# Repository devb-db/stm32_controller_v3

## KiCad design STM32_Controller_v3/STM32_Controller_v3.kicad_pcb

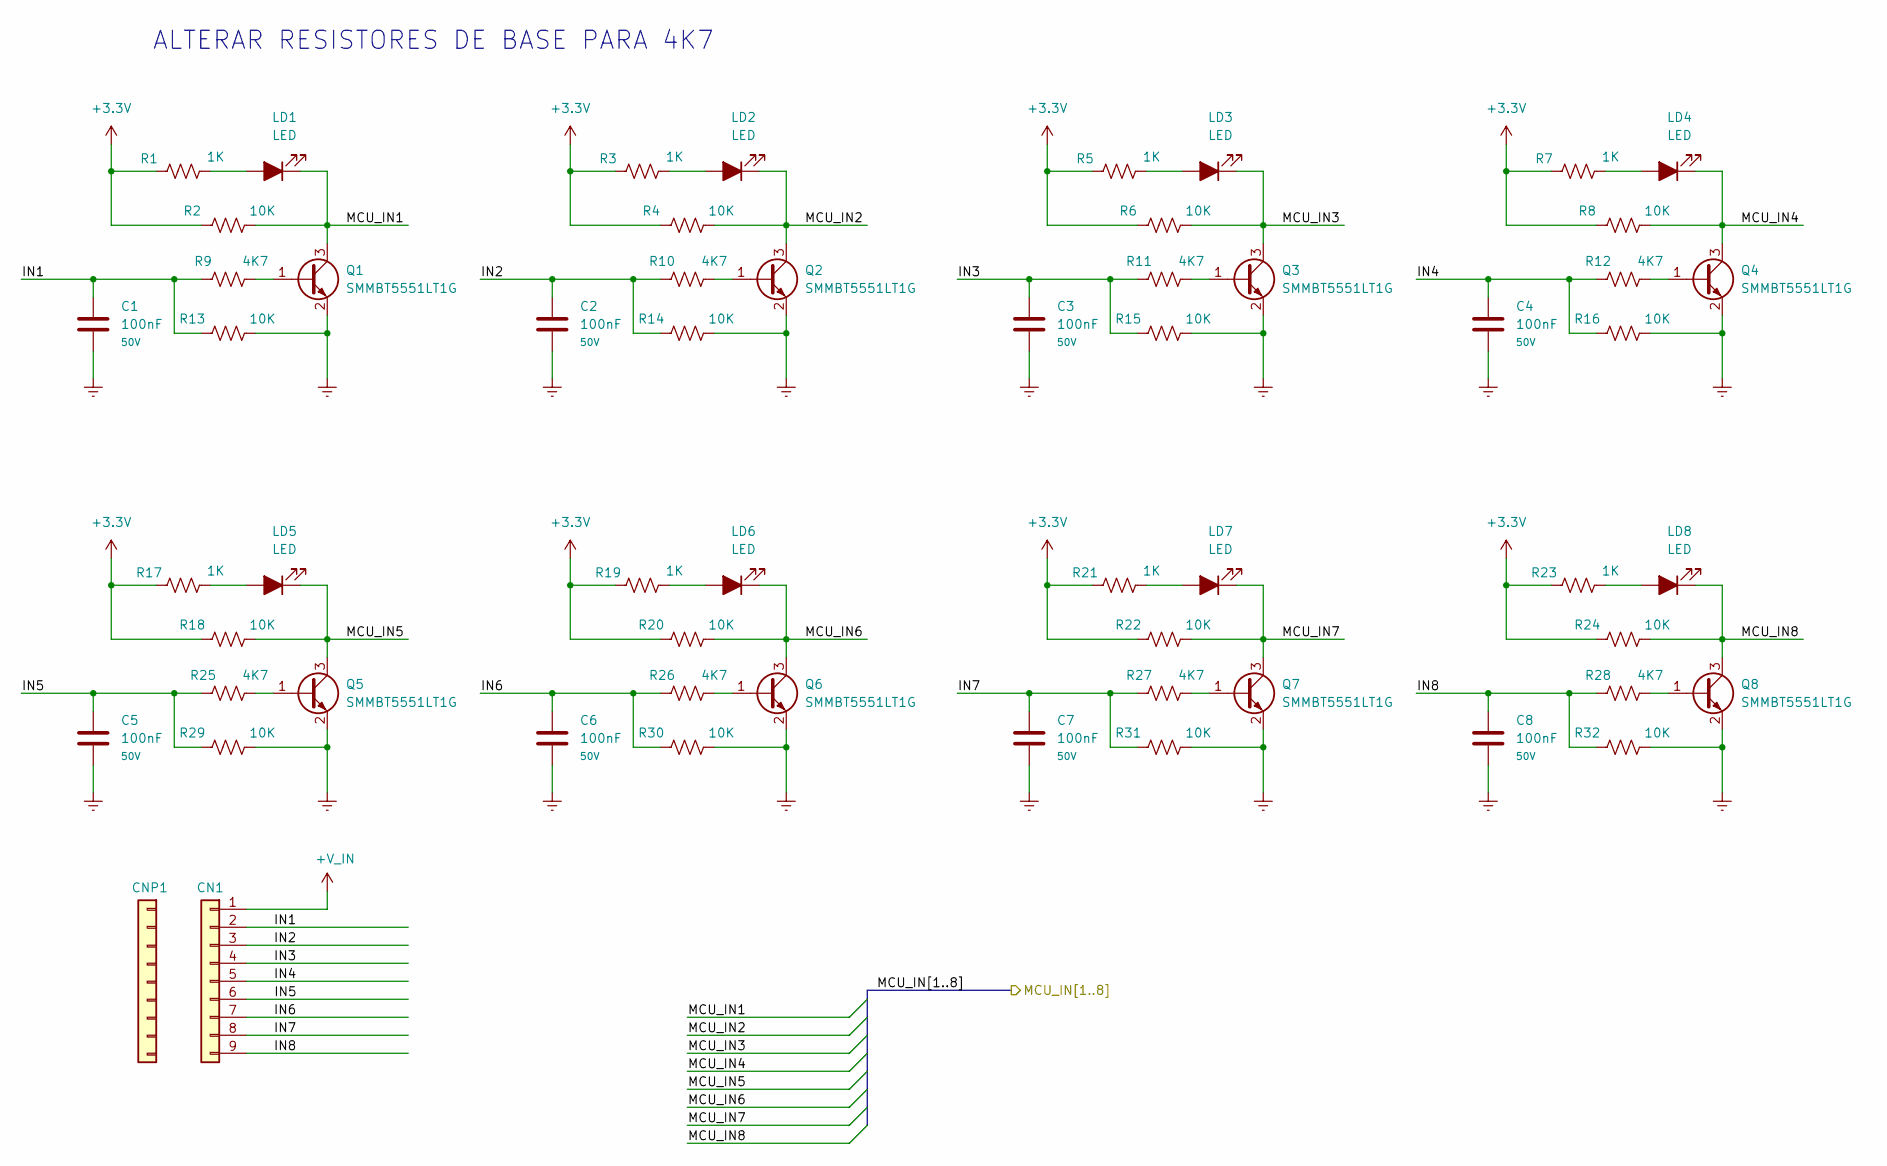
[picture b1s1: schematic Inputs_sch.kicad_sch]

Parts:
C1, C2, C3, C4, C5, C6, C7, C8: 100nF; C_0805; Voltage 50V; Part.Number CC0805KRX7R9BB104; LCSC Part C49678
CN1: WJ15EDGVC-3.81-09P-14-00A; PhoenixContact_MCV_1,5_9-G-3.81_1x09_P3.81mm_Vertical; Part.Number WJ15EDGVC-3.81-09P-14-00A; LCSC Part C49737
CNP1: WJ15EDGK-3.81-09P-14-00A; Part.Number WJ15EDGK-3.81-09P-14-00A; LCSC Part C31287
LD1, LD2, LD3, LD4, LD5, LD6, LD7, LD8: LED; LED_0805_2012Metric; Part.Number NCD0805R1; LCSC Part C84256
Q1, Q2, Q3, Q4, Q5, Q6, Q7, Q8: SMMBT5551LT1G; TSOT-23; Part.Number MMBT5551; LCSC Part C2145
R1, R3, R5, R7, R17, R19, R21, R23: 1K; R_0805; Part.Number 0805W8F1001T5E; LCSC Part C17513
R2, R4, R6, R8, R13, R14, R15, R16, R18, R20, R22, R24, R29, R30, R31, R32: 10K; R_0805; Part.Number 0805W8F1002T5E; LCSC Part C17414
R9, R10, R11, R12, R25, R26, R27, R28: 4K7; R_0805; LCSC Part C17673

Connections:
+3.3V: R1.1, R2.1, R3.1, R4.1, R5.1, R6.1, R7.1, R8.1, R17.1, R18.1, R19.1, R20.1, R21.1, R22.1, R23.1, R24.1; also elsewhere on the board
+V_IN: CN1.1; also elsewhere on the board
/Inputs/IN1: C1.1, CN1.2, R9.1, R13.1
/Inputs/IN2: C2.1, CN1.3, R10.1, R14.1
/Inputs/IN3: C3.1, CN1.4, R11.1, R15.1
/Inputs/IN4: C4.1, CN1.5, R12.1, R16.1
/Inputs/IN5: C5.1, CN1.6, R25.1, R29.1
/Inputs/IN6: C6.1, CN1.7, R26.1, R30.1
/Inputs/IN7: C7.1, CN1.8, R27.1, R31.1
/Inputs/IN8: C8.1, CN1.9, R28.1, R32.1
/Inputs/MCU_IN1: LD1.1 (K), Q1.3 (C), R2.2; also elsewhere on the board
/Inputs/MCU_IN2: LD2.1 (K), Q2.3 (C), R4.2; also elsewhere on the board
/Inputs/MCU_IN3: LD3.1 (K), Q3.3 (C), R6.2; also elsewhere on the board
/Inputs/MCU_IN4: LD4.1 (K), Q4.3 (C), R8.2; also elsewhere on the board
/Inputs/MCU_IN5: LD5.1 (K), Q5.3 (C), R18.2; also elsewhere on the board
/Inputs/MCU_IN6: LD6.1 (K), Q6.3 (C), R20.2; also elsewhere on the board
/Inputs/MCU_IN7: LD7.1 (K), Q7.3 (C), R22.2; also elsewhere on the board
/Inputs/MCU_IN8: LD8.1 (K), Q8.3 (C), R24.2; also elsewhere on the board
GND: C1.2, C2.2, C3.2, C4.2, C5.2, C6.2, C7.2, C8.2, Q1.2 (E), Q2.2 (E), Q3.2 (E), Q4.2 (E), Q5.2 (E), Q6.2 (E), Q7.2 (E), Q8.2 (E), R13.2, R14.2, R15.2, R16.2, R29.2, R30.2, R31.2, R32.2; also elsewhere on the board
unnamed: LD1.2 (A), R1.2
unnamed: LD2.2 (A), R3.2
unnamed: LD3.2 (A), R5.2
unnamed: LD4.2 (A), R7.2
unnamed: LD5.2 (A), R17.2
unnamed: LD6.2 (A), R19.2
unnamed: LD7.2 (A), R21.2
unnamed: LD8.2 (A), R23.2
unnamed: Q1.1 (B), R9.2
unnamed: Q2.1 (B), R10.2
unnamed: Q3.1 (B), R11.2
unnamed: Q4.1 (B), R12.2
unnamed: Q5.1 (B), R25.2
unnamed: Q6.1 (B), R26.2
unnamed: Q7.1 (B), R27.2
unnamed: Q8.1 (B), R28.2

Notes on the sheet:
ALTERAR RESISTORES DE BASE PARA 4K7

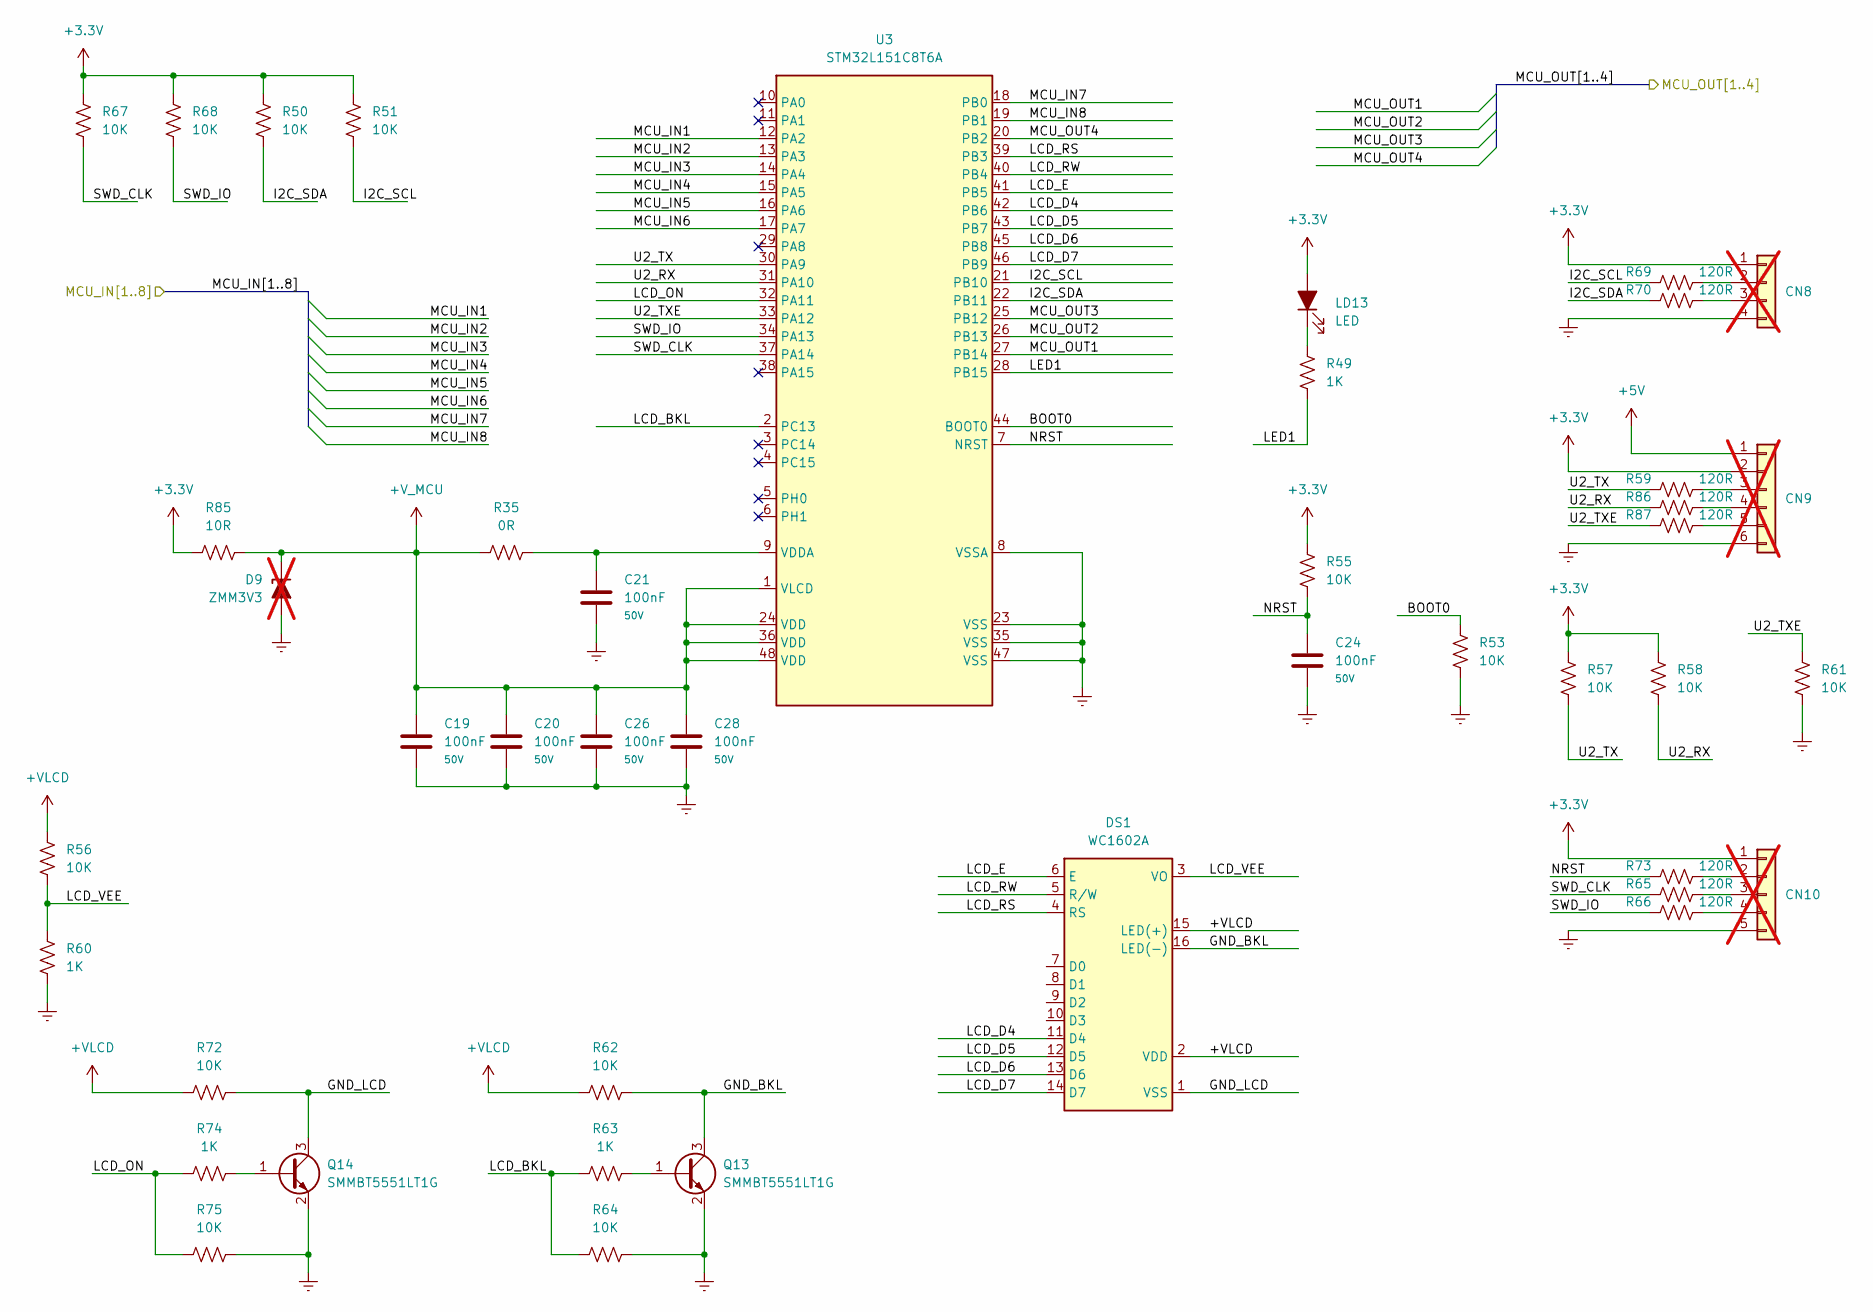
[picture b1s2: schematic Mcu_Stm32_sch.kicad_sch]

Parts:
C19, C20, C21, C24, C26, C28: 100nF; C_0805; Voltage 50V; Part.Number CC0805KRX7R9BB104; LCSC Part C49678
CN8: DS1021-1x4SF11-B; PinHeader_1x04_P2.54mm_Vertical; LCSC Part C7430360; not fitted
CN9: DS1021-1x6SF11-B; PinHeader_1x06_P2.54mm_Vertical; LCSC Part C7430362; not fitted
CN10: DS1021-1x5SF11-B; PinHeader_1x05_P2.54mm_Vertical; LCSC Part C7430361; not fitted
D9: ZMM3V3; D_MiniMELF; LCSC Part C8056; not fitted
DS1: WC1602A; Part.Number MGD1602A-NSW-BBS-01
LD13: LED; LED_0805_2012Metric; Part.Number NCD0805R1; LCSC Part C84256
Q13, Q14: SMMBT5551LT1G; TSOT-23; Part.Number MMBT5551; LCSC Part C2145
R35: 0R; R_0805; Part.Number 0805W8F0000T5E; LCSC Part C17477
R49, R60, R63, R74: 1K; R_0805; Part.Number 0805W8F1001T5E; LCSC Part C17513
R50, R51, R53, R55, R56, R57, R58, R61, R62, R64, R67, R68, R72, R75: 10K; R_0805; Part.Number 0805W8F1002T5E; LCSC Part C17414
R59, R65, R66, R69, R70, R73, R86, R87: 120R; R_0805; Part.Number 0805W8F1200T5E; LCSC Part C17437
R85: 10R; R_0805; Part.Number 0805W8F100JT5E; LCSC Part C17415
U3: STM32L151C8T6A; LQFP-48_7x7mm_P0.5mm; Part.Number STM32L151C8T6; LCSC Part C9861

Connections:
+3.3V: CN8.1, CN9.2, CN10.1, LD13.2 (A), R50.1, R51.1, R55.1, R57.1, R58.1, R67.1, R68.1, R85.1; also elsewhere on the board
+5V: CN9.1; also elsewhere on the board
+VLCD: DS1.2 (VDD), DS1.15 (LED(+)), R56.1, R62.1, R72.1; also elsewhere on the board
+V_MCU: C19.1, C20.1, C26.1, C28.1, D9.1 (K), R35.1, R85.2, U3.1 (VLCD), U3.24 (VDD), U3.36 (VDD), U3.48 (VDD)
/Inputs/MCU_IN1: U3.12 (PA2); also elsewhere on the board
/Inputs/MCU_IN2: U3.13 (PA3); also elsewhere on the board
/Inputs/MCU_IN3: U3.14 (PA4); also elsewhere on the board
/Inputs/MCU_IN4: U3.15 (PA5); also elsewhere on the board
/Inputs/MCU_IN5: U3.16 (PA6); also elsewhere on the board
/Inputs/MCU_IN6: U3.17 (PA7); also elsewhere on the board
/Inputs/MCU_IN7: U3.18 (PB0); also elsewhere on the board
/Inputs/MCU_IN8: U3.19 (PB1); also elsewhere on the board
/Mcu_Stm32/BOOT0: R53.1, U3.44 (BOOT0)
/Mcu_Stm32/GND_BKL: DS1.16 (LED(-)), Q13.3 (C), R62.2
/Mcu_Stm32/GND_LCD: DS1.1 (VSS), Q14.3 (C), R72.2
/Mcu_Stm32/I2C_SCL: R51.2, R69.1, U3.21 (PB10)
/Mcu_Stm32/I2C_SDA: R50.2, R70.1, U3.22 (PB11)
/Mcu_Stm32/LCD_BKL: R63.1, R64.1, U3.2 (PC13)
/Mcu_Stm32/LCD_D4: DS1.11 (D4), U3.42 (PB6)
/Mcu_Stm32/LCD_D5: DS1.12 (D5), U3.43 (PB7)
/Mcu_Stm32/LCD_D6: DS1.13 (D6), U3.45 (PB8)
/Mcu_Stm32/LCD_D7: DS1.14 (D7), U3.46 (PB9)
/Mcu_Stm32/LCD_E: DS1.6 (E), U3.41 (PB5)
/Mcu_Stm32/LCD_ON: R74.1, R75.1, U3.32 (PA11)
/Mcu_Stm32/LCD_RS: DS1.4 (RS), U3.39 (PB3)
/Mcu_Stm32/LCD_RW: DS1.5 (R/W), U3.40 (PB4)
/Mcu_Stm32/LCD_VEE: DS1.3 (VO), R56.2, R60.1
/Mcu_Stm32/LED1: R49.2, U3.28 (PB15)
/Mcu_Stm32/MCU_OUT1: U3.27 (PB14); also elsewhere on the board
/Mcu_Stm32/MCU_OUT2: U3.26 (PB13); also elsewhere on the board
/Mcu_Stm32/MCU_OUT3: U3.25 (PB12); also elsewhere on the board
/Mcu_Stm32/MCU_OUT4: U3.20 (PB2); also elsewhere on the board
/Mcu_Stm32/NRST: C24.1, R55.2, R73.1, U3.7 (NRST)
/Mcu_Stm32/SWD_CLK: R65.1, R67.2, U3.37 (PA14)
/Mcu_Stm32/SWD_IO: R66.1, R68.2, U3.34 (PA13)
/Mcu_Stm32/U2_RX: R58.2, R86.1, U3.31 (PA10)
/Mcu_Stm32/U2_TX: R57.2, R59.1, U3.30 (PA9)
/Mcu_Stm32/U2_TXE: R61.2, R87.1, U3.33 (PA12)
GND: C19.2, C20.2, C21.2, C24.2, C26.2, C28.2, CN8.4, CN9.6, CN10.5, D9.2 (A), Q13.2 (E), Q14.2 (E), R53.2, R60.2, R61.1, R64.2, R75.2, U3.8 (VSSA), U3.23 (VSS), U3.35 (VSS), U3.47 (VSS); also elsewhere on the board
unnamed: CN8.2, R69.2
unnamed: CN8.3, R70.2
unnamed: CN9.3, R59.2
unnamed: CN9.4, R86.2
unnamed: CN9.5, R87.2
unnamed: CN10.2, R73.2
unnamed: CN10.3, R65.2
unnamed: CN10.4, R66.2
unnamed: LD13.1 (K), R49.1
unnamed: Q13.1 (B), R63.2
unnamed: Q14.1 (B), R74.2
unnamed: C21.1, R35.2, U3.9 (VDDA)

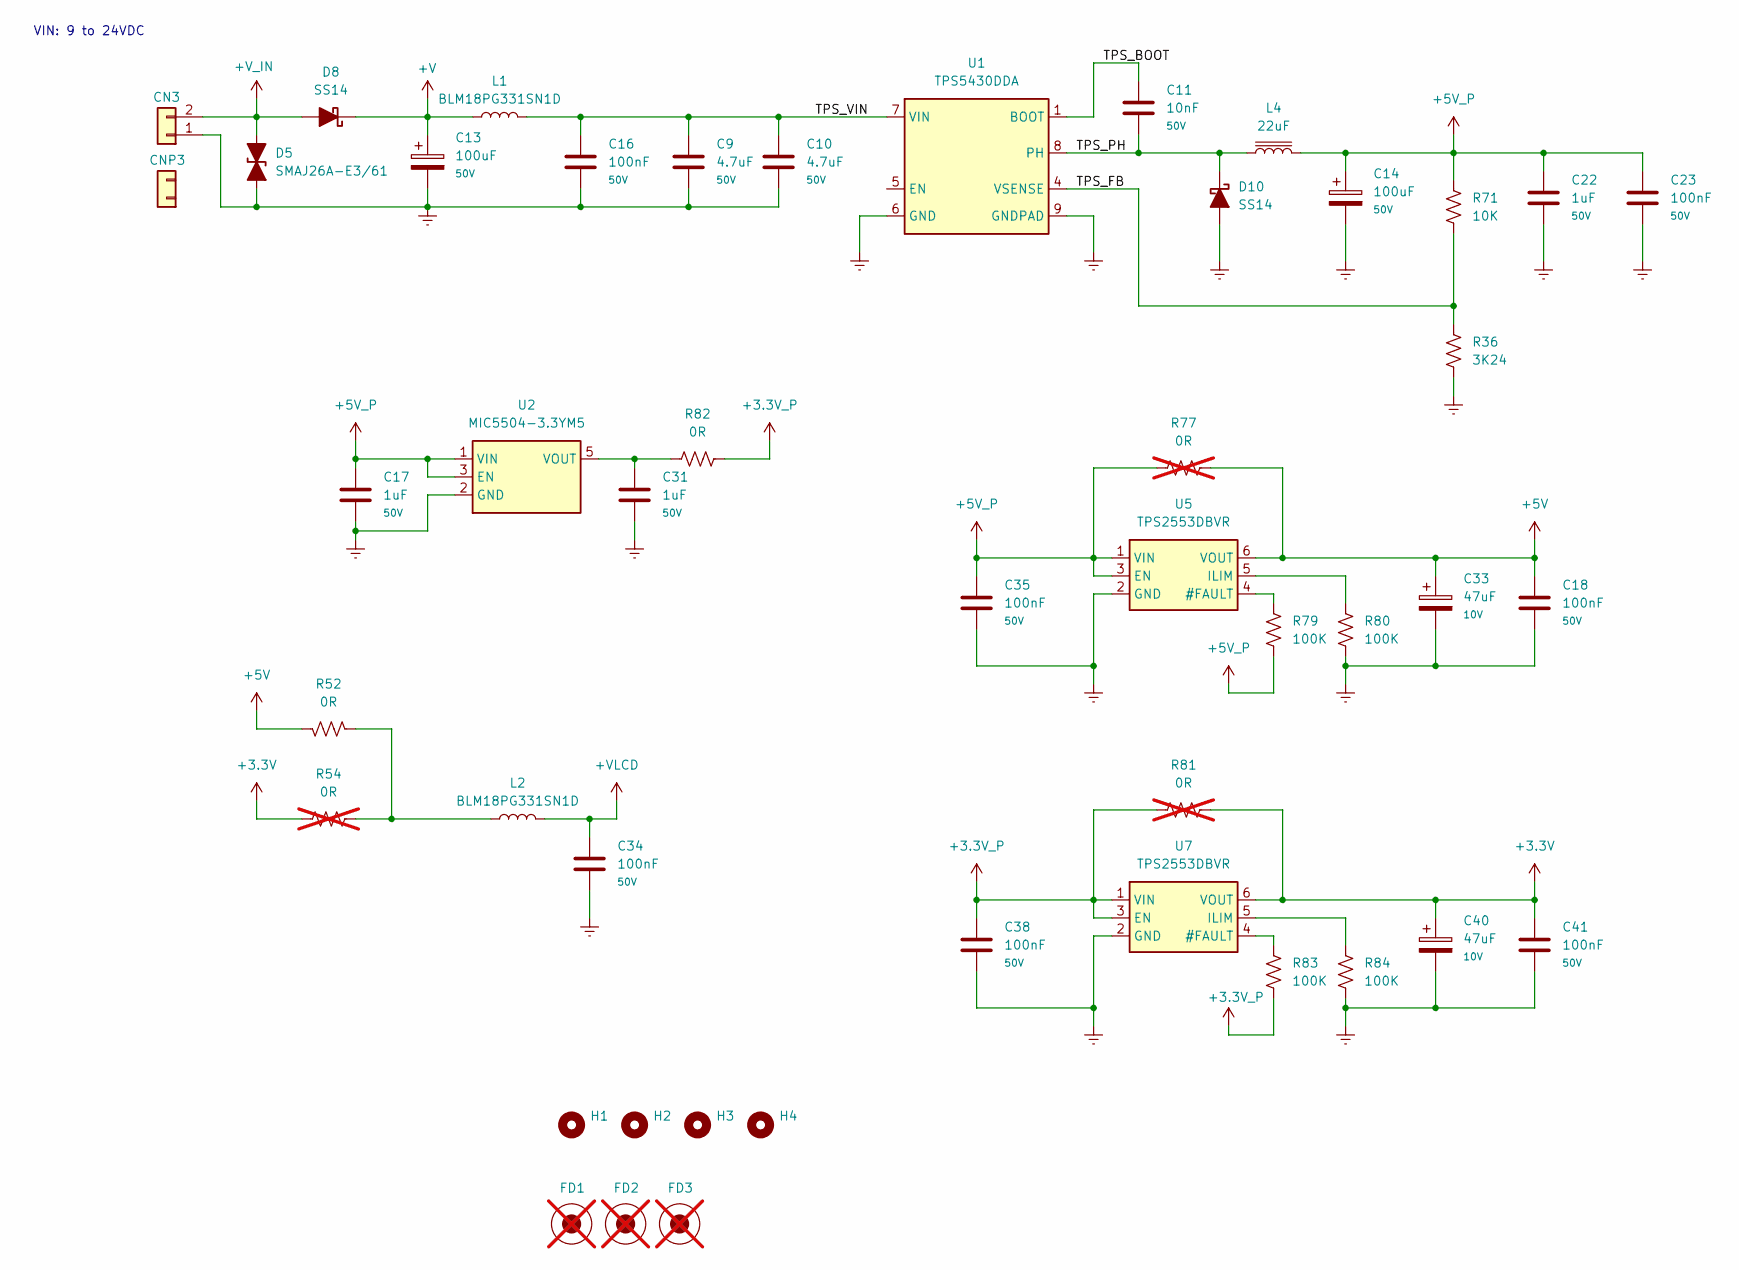
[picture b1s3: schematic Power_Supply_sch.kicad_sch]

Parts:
C9, C10: 4.7uF; C_1206; Voltage 50V; Part.Number 1206B475K500NT; LCSC Part C29823
C11: 10nF; C_0805; Voltage 50V; Part.Number CL21B103KBANNNC; LCSC Part C1710
C13, C14: 100uF; CP_Elec_8x10; Voltage 50V; Part.Number VEJ101M1HTR-0810L; LCSC Part C134502
C16, C18, C23, C34, C35, C38, C41: 100nF; C_0805; Voltage 50V; Part.Number CC0805KRX7R9BB104; LCSC Part C49678
C17, C22, C31: 1uF; C_0805; Voltage 50V; Part.Number CL21B105KBFNNNE; LCSC Part C28323
C33, C40: 47uF; CP_3528-CaseB; Voltage 10V; Part.Number TPSB476K010R0350; LCSC Part C444792
CN3: WJ15EDGVC-3.81-02P-14-00A; PhoenixContact_MCV_1,5_2-G-3.81_1x02_P3.81mm_Vertical; Part.Number WJ15EDGVC-3.81-02P-14-00A; LCSC Part C8396
CNP3: WJ15EDGK-3.81-02P-14-00A; Part.Number WJ15EDGK-3.81-02P-14-00A; LCSC Part C8466
D5: SMAJ26A-E3/61; D_SMA; Part.Number SMAJ26A; LCSC Part C49370
D8, D10: SS14; D_SMA; Part.Number SS14; LCSC Part C2480
FD1, FD2, FD3: FD; Fiducial_1mm_Mask3mm; not fitted
H1, H2, H3, H4: MountingHole; MountingHole_4.3mm_M4_Pad_Via
L1, L2: BLM18PG331SN1D; L_0603_1608Metric; Part.Number BLM18KG601SN1D; LCSC Part C85833
L4: 22uF; L_SMD_6x6x4.5mm; Part.Number FNR6045S220MT; LCSC Part C168080
R36: 3K24; R_0805; Part.Number 0805W8F3241T5E; LCSC Part C17609
R52, R82: 0R; R_0805; Part.Number 0805W8F0000T5E; LCSC Part C17477
R54, R77, R81: 0R; R_0805; LCSC Part C17477; not fitted
R71: 10K; R_0805; Part.Number 0805W8F1002T5E; LCSC Part C17414
R79, R80, R83, R84: 100K; R_0805; Part.Number RC0805FR-07100KL; LCSC Part C96346
U1: TPS5430DDA; TI_SO-PowerPAD-8_ThermalVias; Part.Number TPS5430DDAR; LCSC Part C9864
U2: MIC5504-3.3YM5; SOT-23-5; Part.Number MIC5504-3.3YM5-TR; LCSC Part C88419
U5, U7: TPS2553DBVR; SOT-23-6; Part.Number TPS2553DBVR; LCSC Part C55266

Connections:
+3.3V: C40.1, C41.1, R54.1, R81.2, U7.6 (VOUT); also elsewhere on the board
+3.3V_P: C38.1, R81.1, R82.2, R83.2, U7.1 (VIN), U7.3 (EN)
+5V: C18.1, C33.1, R52.2, R77.2, U5.6 (VOUT); also elsewhere on the board
+5V_P: C14.1, C17.1, C22.1, C23.1, C35.1, L4.2, R71.1, R77.1, R79.2, U2.1 (VIN), U2.3 (EN), U5.1 (VIN), U5.3 (EN)
+V: C13.1, D8.1 (K), L1.1
+VLCD: C34.1, L2.2; also elsewhere on the board
+V_IN: CN3.2, D5.2 (A2), D8.2 (A); also elsewhere on the board
/Power_Supply/TPS_BOOT: C11.1, U1.1 (BOOT)
/Power_Supply/TPS_FB: R36.1, R71.2, U1.4 (VSENSE)
/Power_Supply/TPS_PH: C11.2, D10.1 (K), L4.1, U1.8 (PH)
/Power_Supply/TPS_VIN: C9.1, C10.1, C16.1, L1.2, U1.7 (VIN)
GND: C9.2, C10.2, C13.2, C14.2, C16.2, C17.2, C18.2, C22.2, C23.2, C31.2, C33.2, C34.2, C35.2, C38.2, C40.2, C41.2, CN3.1, D5.1 (A1), D10.2 (A), R36.2, R80.2, R84.2, U1.6 (GND), U1.9 (GNDPAD), U2.2 (GND), U5.2 (GND), U7.2 (GND); also elsewhere on the board
unnamed: L2.1, R52.1, R54.2
unnamed: C31.1, R82.1, U2.5 (VOUT)
unnamed: R79.1, U5.4 (#FAULT)
unnamed: R80.1, U5.5 (ILIM)
unnamed: R83.1, U7.4 (#FAULT)
unnamed: R84.1, U7.5 (ILIM)

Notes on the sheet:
VIN: 9 to 24VDC

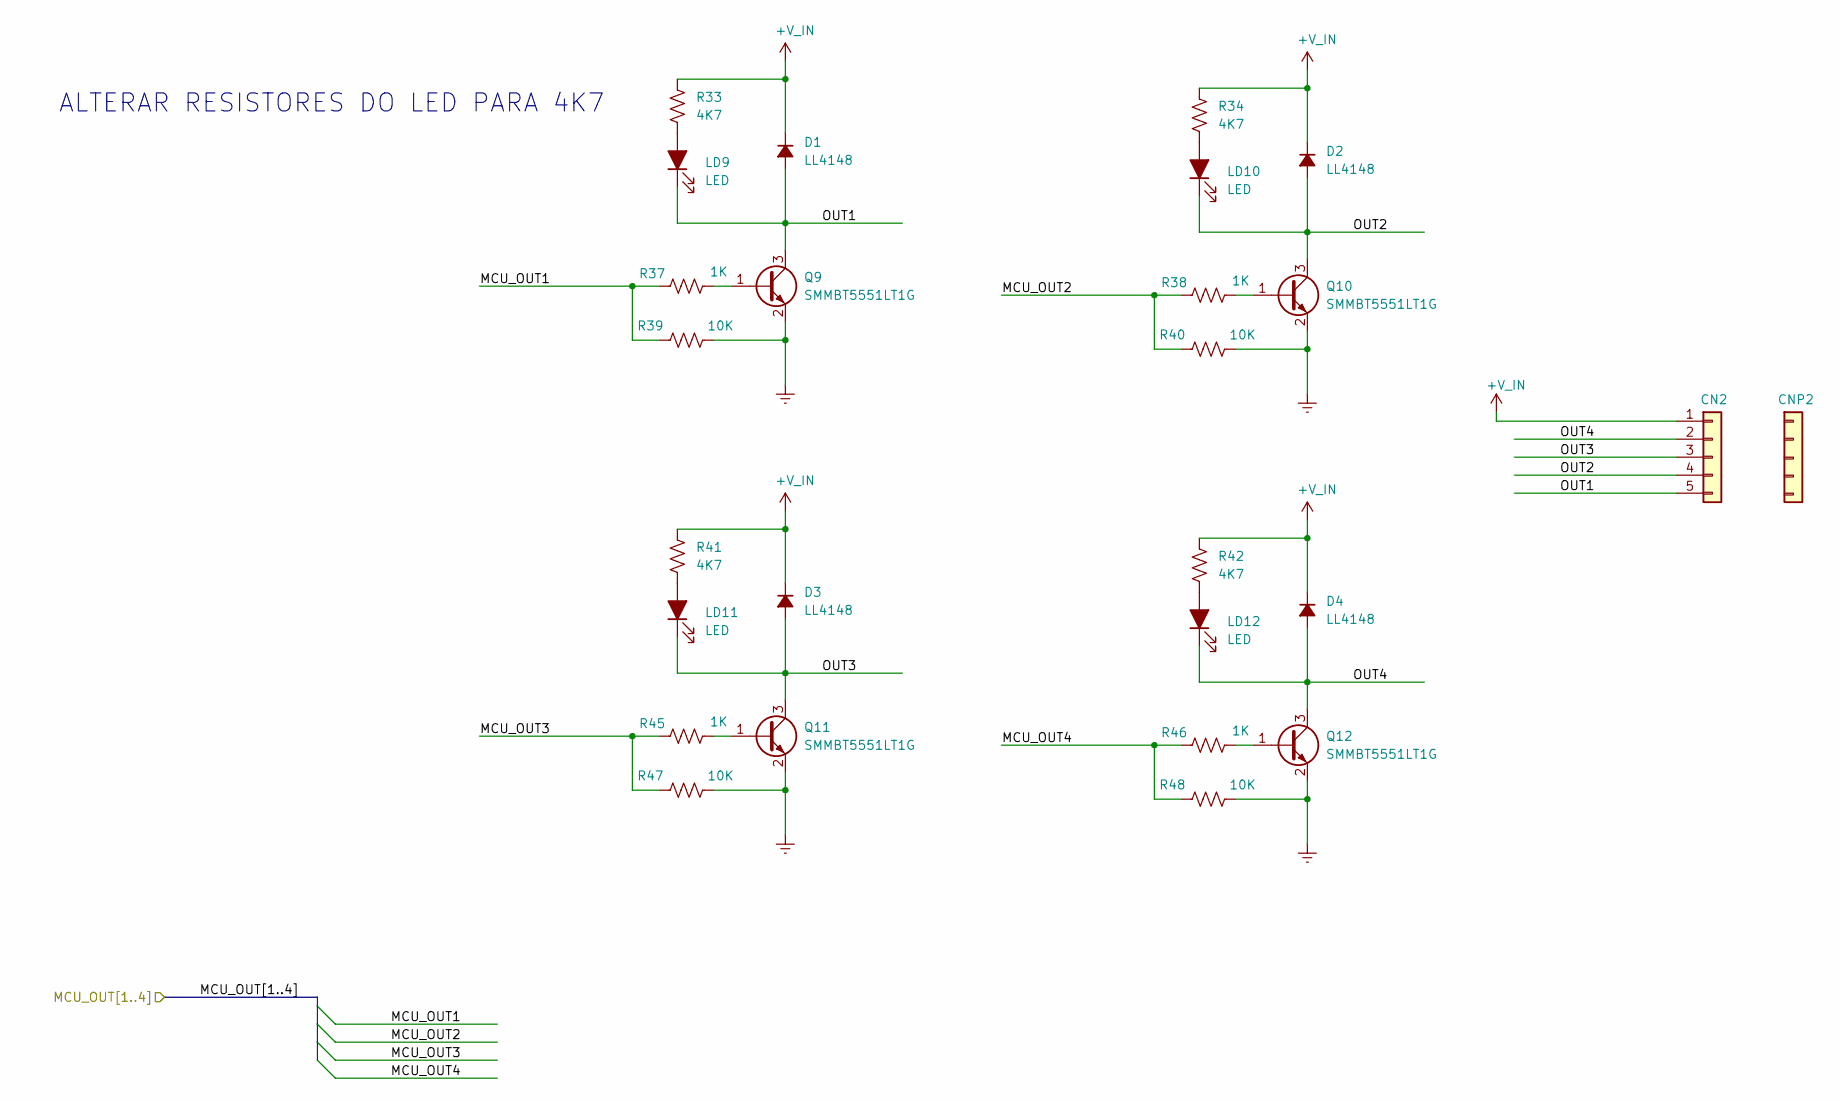
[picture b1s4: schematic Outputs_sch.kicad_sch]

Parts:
CN2: WJ15EDGVC-3.81-05P-14-00A; PhoenixContact_MCV_1,5_5-G-3.81_1x05_P3.81mm_Vertical; Part.Number WJ15EDGVC-3.81-05P-14-00A; LCSC Part C8391
CNP2: WJ15EDGK-3.81-05P-14-00A; Part.Number WJ15EDGK-3.81-05P-14-00A; LCSC Part C3804
D1, D2, D3, D4: LL4148; D_MiniMELF; Part.Number LL4148; LCSC Part C84062
LD9, LD10, LD11, LD12: LED; LED_0805_2012Metric; Part.Number NCD0805R1; LCSC Part C84256
Q9, Q10, Q11, Q12: SMMBT5551LT1G; TSOT-23; Part.Number MMBT5551; LCSC Part C2145
R33, R34, R41, R42: 4K7; R_0805; LCSC Part C17673
R37, R38, R45, R46: 1K; R_0805; Part.Number 0805W8F1001T5E; LCSC Part C17513
R39, R40, R47, R48: 10K; R_0805; Part.Number 0805W8F1002T5E; LCSC Part C17414

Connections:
+V_IN: CN2.1, D1.1 (K), D2.1 (K), D3.1 (K), D4.1 (K), R33.1, R34.1, R41.1, R42.1; also elsewhere on the board
/Mcu_Stm32/MCU_OUT1: R37.1, R39.1; also elsewhere on the board
/Mcu_Stm32/MCU_OUT2: R38.1, R40.1; also elsewhere on the board
/Mcu_Stm32/MCU_OUT3: R45.1, R47.1; also elsewhere on the board
/Mcu_Stm32/MCU_OUT4: R46.1, R48.1; also elsewhere on the board
/Outputs/OUT1: CN2.5, D1.2 (A), LD9.1 (K), Q9.3 (C)
/Outputs/OUT2: CN2.4, D2.2 (A), LD10.1 (K), Q10.3 (C)
/Outputs/OUT3: CN2.3, D3.2 (A), LD11.1 (K), Q11.3 (C)
/Outputs/OUT4: CN2.2, D4.2 (A), LD12.1 (K), Q12.3 (C)
GND: Q9.2 (E), Q10.2 (E), Q11.2 (E), Q12.2 (E), R39.2, R40.2, R47.2, R48.2; also elsewhere on the board
unnamed: LD9.2 (A), R33.2
unnamed: LD10.2 (A), R34.2
unnamed: LD11.2 (A), R41.2
unnamed: LD12.2 (A), R42.2
unnamed: Q9.1 (B), R37.2
unnamed: Q10.1 (B), R38.2
unnamed: Q11.1 (B), R45.2
unnamed: Q12.1 (B), R46.2

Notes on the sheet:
ALTERAR RESISTORES DO LED PARA 4K7

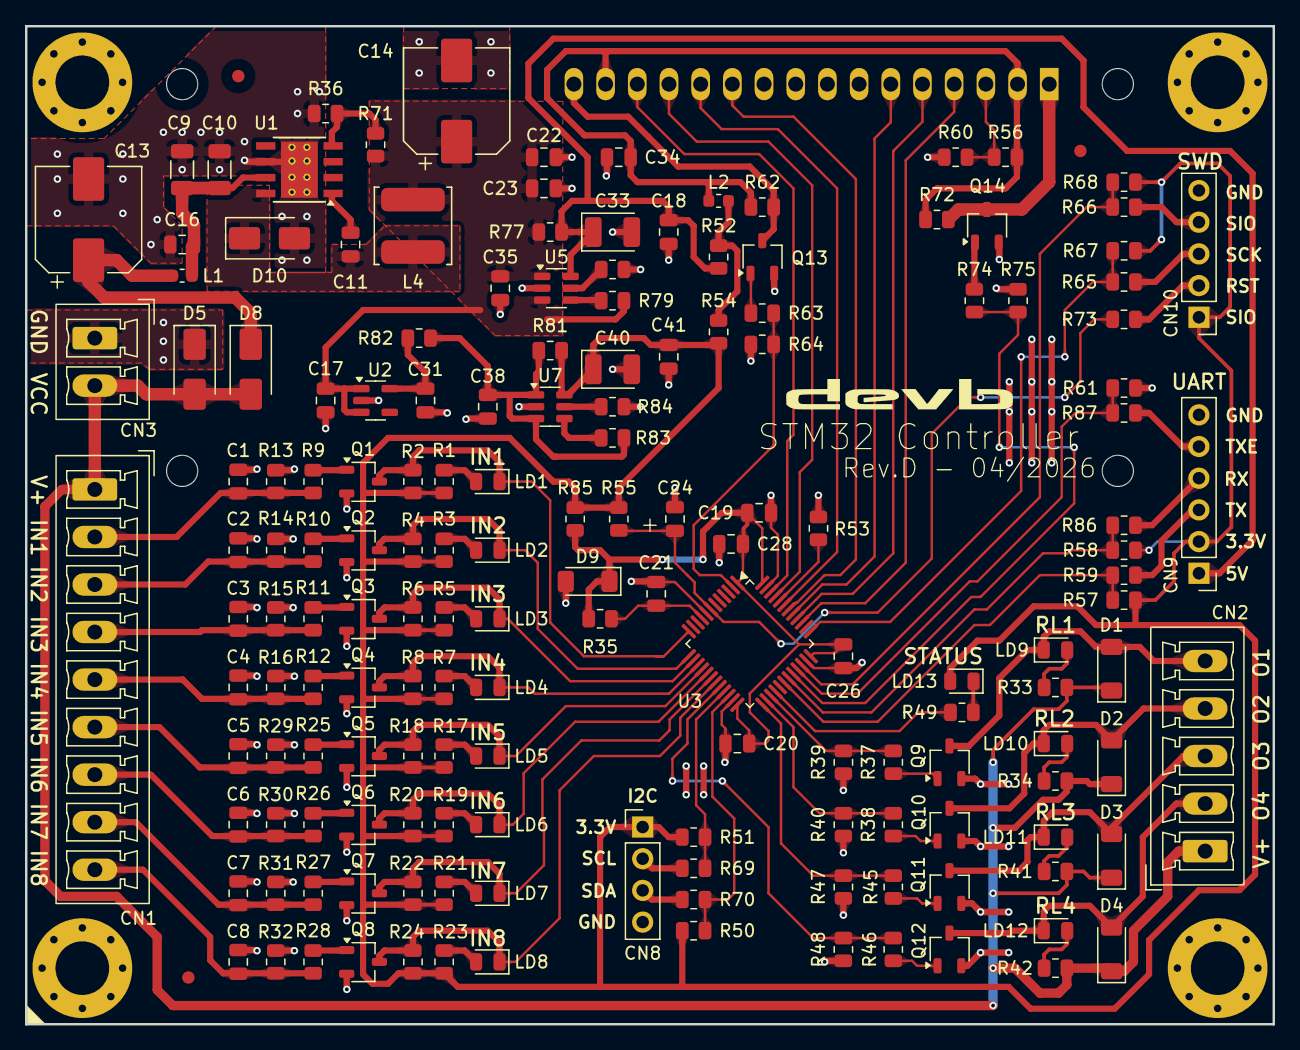
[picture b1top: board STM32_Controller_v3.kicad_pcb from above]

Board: 2 copper layers, 100.0 x 80.0 mm, 172 parts (1 on the bottom side), 101 nets.

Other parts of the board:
G1: LOGO; logo_devb_h

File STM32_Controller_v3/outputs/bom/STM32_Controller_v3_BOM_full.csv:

"Comment","Designator","Footprint","LCSC Part","Part.Number","Manufacturer","Assembly"
"Resistor, 4.7 KOhm, 1%, 0.125 W, -55 to 155 degC, 0805","R9,R10,R11,R12,R25,R26,R27,R28,R33,R34,R41,R42","db_resistors:R_0805","C17673","","",""
"Header 3.81mm, 9W, 180° 300V","CN1","Library:PhoenixContact_MCV_1,5_9-G-3.81_1x09_P3.81mm_Vertical","C49737","WJ15EDGVC-3.81-09P-14-00A","KANGNEX","PTH"
"Header 3.81mm, 5W, 180° 300V","CN2","Library:PhoenixContact_MCV_1,5_5-G-3.81_1x05_P3.81mm_Vertical","C8391","WJ15EDGVC-3.81-05P-14-00A","KANGNEX","PTH"
"Header 3.81mm, 2W, 180° 300V","CN3","Library:PhoenixContact_MCV_1,5_2-G-3.81_1x02_P3.81mm_Vertical","C8396","WJ15EDGVC-3.81-02P-14-00A","KANGNEX","PTH"
"Plug 3.81mm, 9W, 180°, 300V","CNP1","","C31287","WJ15EDGK-3.81-09P-14-00A","KANGNEX","PTH"
"Plug 3.81mm, 5W, 180°, 300V","CNP2","","C3804","WJ15EDGK-3.81-05P-14-00A","KANGNEX","PTH"
"Plug 3.81mm, 2W, 180°, 300V","CNP3","","C8466","WJ15EDGK-3.81-02P-14-00A","KANGNEX","PTH"
"LCD 16x2 Alphanumeric , 8 bit parallel bus, 5V VDD","DS1","Library:WC1602A","","MGD1602A-NSW-BBS-01","","PTH"
"Capacitor MLCC SMT 50V 100nF X7R 0805 10%","C1,C2,C3,C4,C5,C6,C7,C8,C16,C18,C19,C20,C21,C23,C24,C26,C28,C34,C35,C38,C41","Library:C_0805","C49678","CC0805KRX7R9BB104","YAGEO","SMT"
"Capacitor MLCC SMT 50V 4.7uF X7R 1206 10%","C9,C10","Library:C_1206","C29823","1206B475K500NT","FH","SMT"
"Capacitors MLCC SMT 50V 10nF X7R 0805 10%","C11","Library:C_0805","C1710","CL21B103KBANNNC","Samsung Electro-Mechanics","SMT"
"Aluminum Electrolytic Capacitor 100uF, 50 V, +/- 20%, -55 to 105 degC, 8x10mm DxL","C13,C14","Library:CP_Elec_8x10","C134502","VEJ101M1HTR-0810L","Lelon","SMT"
"Capacitor MLCC SMT 50V 1uF X7R 0805 10%","C17,C22,C31","Library:C_0805","C28323","CL21B105KBFNNNE","Samsung Electro-Mechanics","SMT"
"Tantalum Capacitor 47uF, 10 V, +/- 20%, -55 to 125 degC, CaseB","C33,C40","Library:CP_3528-CaseB","C444792","TPSB476K010R0350","Kyocera AVX","SMT"
"LL4148, LL-34 Switching Diodes ROHS","D1,D2,D3,D4","Library:D_MiniMELF","C84062","LL4148","Changzhou Starsea Elec","SMT"
"TVS DO-214AC(SMA) 26V (9.5A) ESD and Surge Protection","D5","Library:D_SMA","C49370","SMAJ26A","RUILON","SMT"
"SS14 - Diode, Schottky, 1a, 40v, DO-214AC","D8,D10","Library:D_SMA","C2480","SS14","MDD(Microdiode Semiconductor)","SMT"
"600Ω @ 100MHz 1 1.3A 150mΩ 0603 Ferrite Bead","L1,L2","Library:L_0603_1608Metric","C85833","BLM18KG601SN1D","muRata","SMT"
"116mΩ 22uH 2A Magnetic Shielded Inductor ±20% SMD,6x6mm Power Inductors","L4","Library:L_SMD_6x6x4.5mm","C168080","FNR6045S220MT","cjiang","SMT"
"LED 0805 Red","LD1,LD2,LD3,LD4,LD5,LD6,LD7,LD8,LD9,LD10,LD11,LD12,LD13","Library:LED_0805_2012Metric","C84256","NCD0805R1","NATIONSTAR","SMT"
"NPN transistor, base/emitter/collector","Q1,Q2,Q3,Q4,Q5,Q6,Q7,Q8,Q9,Q10,Q11,Q12,Q13,Q14","Library:TSOT-23","C2145","MMBT5551","JSCJ","SMT"
"Resistor, 1 KOhm, 1%, 0.125 W, -55 to 155 degC, 0805","R1,R3,R5,R7,R17,R19,R21,R23,R37,R38,R45,R46,R49,R60,R63,R74","Library:R_0805","C17513","0805W8F1001T5E","UNI-ROYAL","SMT"
"Resistor, 10 KOhm, 1%, 0.125 W, -55 to 155 degC, 0805","R2,R4,R6,R8,R13,R14,R15,R16,R18,R20,R22,R24,R29,R30,R31,R32,R39,R40,R47,R48,R50,R51,R53,R55,R56,R57,R58,R61,R62,R64,R67,R68,R71,R72,R75","Library:R_0805","C17414","0805W8F1002T5E","UNI-ROYAL","SMT"
"Resistor, 0 Ohm, -55 to 155 degC, 0805","R35,R52,R82","Library:R_0805","C17477","0805W8F0000T5E","UNI-ROYAL","SMT"
"Resistor, 3.24 KOhm, 1%, 0.125 W, -55 to 155 degC, 0805","R36","db_resistors:R_0805","C17609","0805W8F3241T5E","UNI-ROYAL","SMT"
"Resistor, 120 Ohm, 1%, 0.125 W, -55 to 155 degC, 0805","R59,R65,R66,R69,R70,R73,R86,R87","Library:R_0805","C17437","0805W8F1200T5E","UNI-ROYAL","SMT"
"Resistor, 100 KOhm, 1%, 0.125 W, -55 to 155 degC, 0805","R79,R80,R83,R84","Library:R_0805","C96346","RC0805FR-07100KL","YAGEO","SMT"
"Resistor, 10 Ohm, 1%, 0.125 W, -55 to 155 degC, 0805","R85","Library:R_0805","C17415","0805W8F100JT5E","UNI-ROYAL","SMT"
"3A, Step Down Swift Converter, Adjustable Output Voltage, 5.5-36V Input Voltage, PowerSO-8","U1","Library:TI_SO-PowerPAD-8_ThermalVias","C9864","TPS5430DDAR","TI","SMT"
"300mA Low-dropout Voltage Regulator, Vout 3.3V, Vin up to 5.5V, SOT-23-5","U2","Library:SOT-23-5","C88419","MIC5504-3.3YM5-TR","MICROCHIP","SMT"
"ARM Microcontrollers - MCU Ultra-low-power Arm Cortex-M3 MCU 64 Kbytes of Flash , 32 MHz CPU, USB","U3","Library:LQFP-48_7x7mm_P0.5mm","C9861","STM32L151C8T6","ST","SMT"
"5.5V, 2.1A, Adjustable Current Limiting Power Distribution Switch, SOT-23-6","U5,U7","Library:SOT-23-6"," C55266","TPS2553DBVR","TI","SMT"

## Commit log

2026-04-17 project upload
2026-04-30 production version
2026-06-01 update dimension information
2026-06-17 res 4k7 in digital inputs and outputs leds
